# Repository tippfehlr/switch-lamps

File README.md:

# switch-lamps

A switch for all my lamps 🛋️

## Goals

- Making it possible to control all lamps from one place
- Making multiple switches work together (no state stored on the switch unit)
- Needs to be foolproof
- Adding new lamps should be reasonably easy

## Hardware

### Lamps

Communication over a serial connection.

- One long wall with lamps
  - 4 zones
  - one warm and one cold led strip per zone
- 3 table lamps
- ceiling lamps
- a few floor lamps
- possibly more lamps in the future

### Inputs

- Slide up/down/left/right
- Press up/down/left/right
- Rotate left/right
- a proximity sensor

Sliding always also presses the corresponding button,
so sliding has to overwrite pressing.

### Outputs

- a Waveshare 1.54" B/W e-paper display
- the lamps, obviously

PCB design in `hardware/`.

### Microcontroller

Arduino ProMini 3.3V (8MHz)

The switch is powered over a long wire without much throughput,
which is also why the capacitors are needed.
They provide a buffer for updating the display.

## Software

- [avr-hal](https://github.com/Rahix/avr-hal) (currently my [fork](https://github.com/tippfehlr/avr-hal/tree/sparkfun-promini-3.3v) for `sparkfun-promini-3v3` support)
- [epd-waveshare](https://github.com/caemor/epd-waveshare) and [embedded-graphics](https://github.com/embedded-graphics/embedded-graphics) for the display

## current state

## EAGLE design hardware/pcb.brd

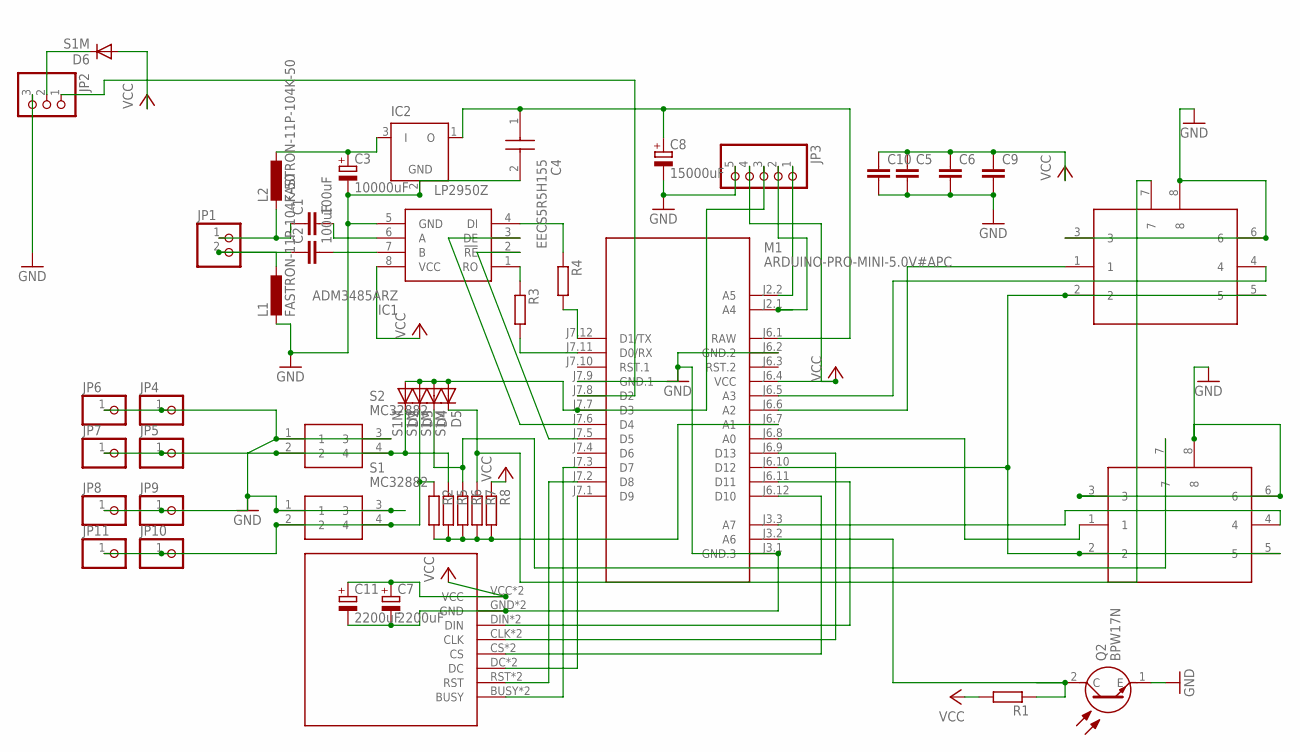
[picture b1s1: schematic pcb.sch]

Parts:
C1, C2: 100uF; C1210
C3: 10000uF; E7,5-18
C4: EECS5R5H155; SG(H)
C5, C6, C9, C10: C-EUC1812; C1812
C7, C11: 2200uF; TT5D9
C8: 15000uF; E7,5-18
D2, D3, D4, D5, D6: S1M; SMA
IC1: ADM3485ARZ; SOIC127P600X175-8N
IC2: LP2950Z; TO92
JP1: PINHD-1X2; 1X02
JP2: PINHD-1X3; 1X03
JP3: PINHD-1X55X2MM; 1_05X2MM
JP4, JP5, JP6, JP7, JP8, JP9, JP10, JP11: PINHD-1X1; 1X01
L1, L2: FASTRON-11P-104K-50; E5-10,5
M1: ARDUINO-PRO-MINI-5.0V#APC; ARDUINO-PRO-MINI#APC
Q2: BPW17N
R1, R2, R3, R4, R5, R6, R7, R8: R-EU_R1206; R1206
S1, S2: MC32882
U$1, U$2: FJ08K-S
U$3: 1,54-E-PAPER

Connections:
A: C1.2, IC1.6 (A)
A1: C1.1, JP1.1, L2.- (2)
B: C2.2, IC1.7 (B)
B1: C2.1, JP1.2, L1.+ (1)
GND: C3.-, C4.2, C5.2, C6.2, C7.-, C8.-, C9.2, C10.2, C11.-, IC1.5 (GND), IC2.2 (GND), JP2.3, JP3.5, JP4.1, JP6.1, JP8.1, JP9.1, L1.- (2), M1.J3.1 (GND.3), M1.J6.2 (GND.2), M1.J7.9 (GND.1), Q2.1 (E), S1.1, S1.3, S2.1, S2.3, U$1.3, U$1.6, U$1.8, U$2.3, U$2.6, U$2.8, U$3.GND, U$3.GND1 (GND)
unnamed: M1.J6.8 (A0), U$2.1
unnamed: D2.C, JP5.1, JP7.1, R5.1, S2.2, S2.4
unnamed: JP3.1, M1.J2.2 (A5)
unnamed: M1.J7.3 (D7), U$3.BUSY, U$3.BUSY1 (BUSY)
unnamed: M1.J7.2 (D8), U$3.RST, U$3.RST1 (RST)
unnamed: M1.J7.1 (D9), U$3.DC, U$3.DC1 (DC)
unnamed: M1.J6.12 (D10), U$3.CS, U$3.CS1 (CS)
unnamed: M1.J6.9 (D13), U$3.CLK, U$3.CLK1 (CLK)
unnamed: M1.J6.11 (D11), U$3.DIN, U$3.DIN1 (DIN)
unnamed: M1.J6.10 (D12), U$1.2, U$1.5, U$2.2, U$2.5
unnamed: M1.J3.3 (A7), U$2.4
unnamed: D5.C, R7.1, U$1.7
unnamed: M1.J6.6 (A2), U$1.1
unnamed: M1.J6.5 (A3), U$1.4
unnamed: D4.C, R6.1, U$2.7
unnamed: M1.J3.2 (A6), Q2.2 (C), R1.1
unnamed: M1.J7.11 (D0/RX), R3.2
unnamed: C3.+, IC2.3 (I), L2.+ (1)
unnamed: IC1.3 (DE), M1.J7.6 (D4)
unnamed: IC1.4 (DI), R4.1
unnamed: M1.J7.12 (D1/TX), R4.2
unnamed: D6.C, JP2.2
unnamed: IC1.1 (RO), R3.1
unnamed: JP2.1, M1.J7.8 (D2)
unnamed: IC1.2 (!RE), M1.J7.5 (D5)
unnamed: M1.J6.7 (A1), R2.2, R5.2, R6.2, R7.2, R8.2
unnamed: D2.A, D3.A, D4.A, D5.A, JP3.3, M1.J7.7 (D3)
unnamed: JP3.2, M1.J2.1 (A4)
unnamed: D3.C, JP10.1, JP11.1, R2.1, S1.2, S1.4
RAW: C4.1, C8.+, IC2.1 (O), M1.J6.1 (RAW)
VCC: C5.1, C6.1, C7.+, C9.1, C10.1, C11.+, D6.A, IC1.8 (VCC), JP3.4, M1.J6.4 (VCC), R1.2, R8.1, U$3.VCC, U$3.VCC1 (VCC)

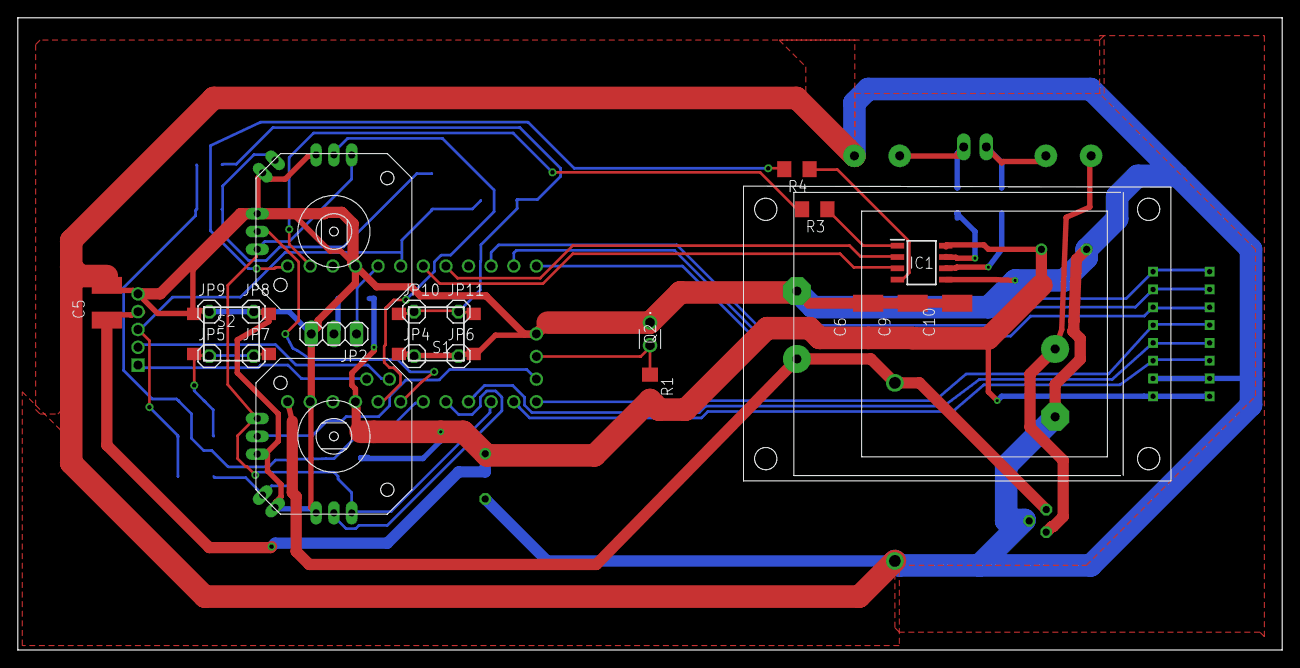
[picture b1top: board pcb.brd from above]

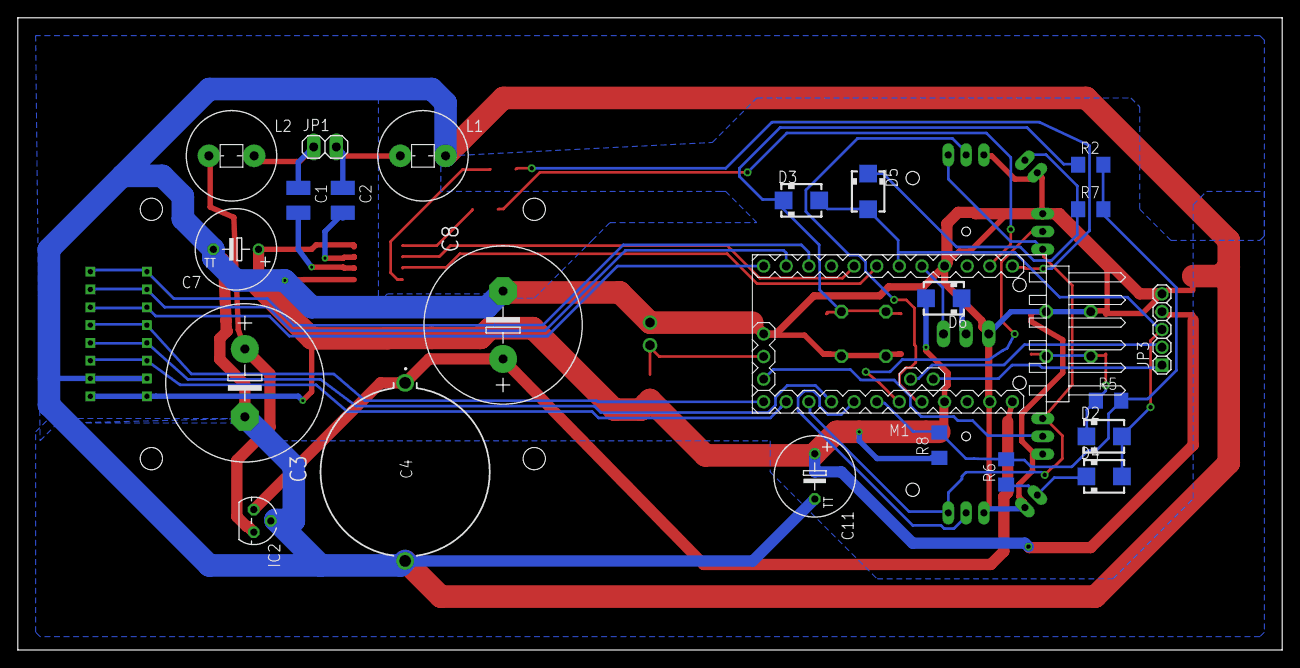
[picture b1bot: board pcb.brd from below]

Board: 2 copper layers, 142.0 x 71.0 mm, 46 parts (23 on the bottom side), 36 nets.

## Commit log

2023-02-22 initial commit -- working blinky
2023-03-03 MenuState
2023-03-28 working millis(), interface model
2023-03-29 button & menu control structure
2023-05-09 [not compiling] WIP: display setup
2023-05-29 DisplayBuffer struct commented out, otherwise compiling without errors
2023-06-08 dyn WaveshareDisplay is working but is dynamic. Epd1in54 should work but doesn’t
    WaveshareDisplay<SPI, Output, Input, Output, Output, Delay, DisplayColor = BinaryColor>
    Epd1in54<SPI, Output, Input, Output, Output, Delay>
2023-06-09 Epd1in54 and DisplayTarget are working
2023-06-09 impl clear() | display is fully compiling
2023-06-13 finish display struct & write simple text on display
2023-06-15 print raw data
2023-06-20 working & tested
    hand not yet working
2023-11-29 chore(deps): update dependencies
2023-11-29 chore(style): remove whitespace/comments
2024-01-14 refactor: use the sparkfun-promini-3v board from arduino-hal
2024-01-14 refactor: use sparkfun-promini-3v from arduino-hal
2024-01-14 fix: reverse slide/press direction
2024-01-14 chore: add justfile for easy running with `just run`
2024-01-14 chore: add .editorconfig
2024-01-20 chore: update .gitignore
2024-01-20 style: set indent_size to 4
2024-01-20 add hardware files
2024-01-20 chore: rename to switch-lamps
2024-01-20 docs: add readme explaining the project
2024-01-20 wip: uncomment display/epd, rename lamps, make pins static
2024-01-21 docs: add microcontroller part to readme
2024-01-21 docs: update readme
2024-05-18 chore: move everything to switch/
2024-05-18 chore: move avr-specs to switch and create link from root
    apparently rust-analyzer expects it to be in the Cargo.toml folder, but
    cargo run needs it to be in the git root
2024-05-19 chore: specify port and baud rate in .cargo/config.toml
2024-05-19 chore: use 115200, remove tabs
2024-05-19 working with binary interface
2024-05-23 fix: reset menu timeout when any button is pressed, add 0x00 to beginning of message
2024-05-23 chore(deps): use Rahix’s version of avr-hal, rev-bound
    my repo was only for testing the poti bug
2024-05-23 chore(deps): update deps
2024-05-23 chore: use tippfehlr/ravedude with output-mode decimal
2024-05-23 fix: millis now uses arduino_hal::DefaultClock based on enabled features
2024-05-23 feat: set change rate per seconds to fix amount, set updates per second
2024-05-24 refactor: use for in for 6x 0x00
2024-08-18 feat: add sleep functions, disable display mode switching for now

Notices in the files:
parts and their libraries:
diy-modules: Released under the Creative Commons Attribution 4.0 International License: http://creativecommons.org/licenses/by/4.0
